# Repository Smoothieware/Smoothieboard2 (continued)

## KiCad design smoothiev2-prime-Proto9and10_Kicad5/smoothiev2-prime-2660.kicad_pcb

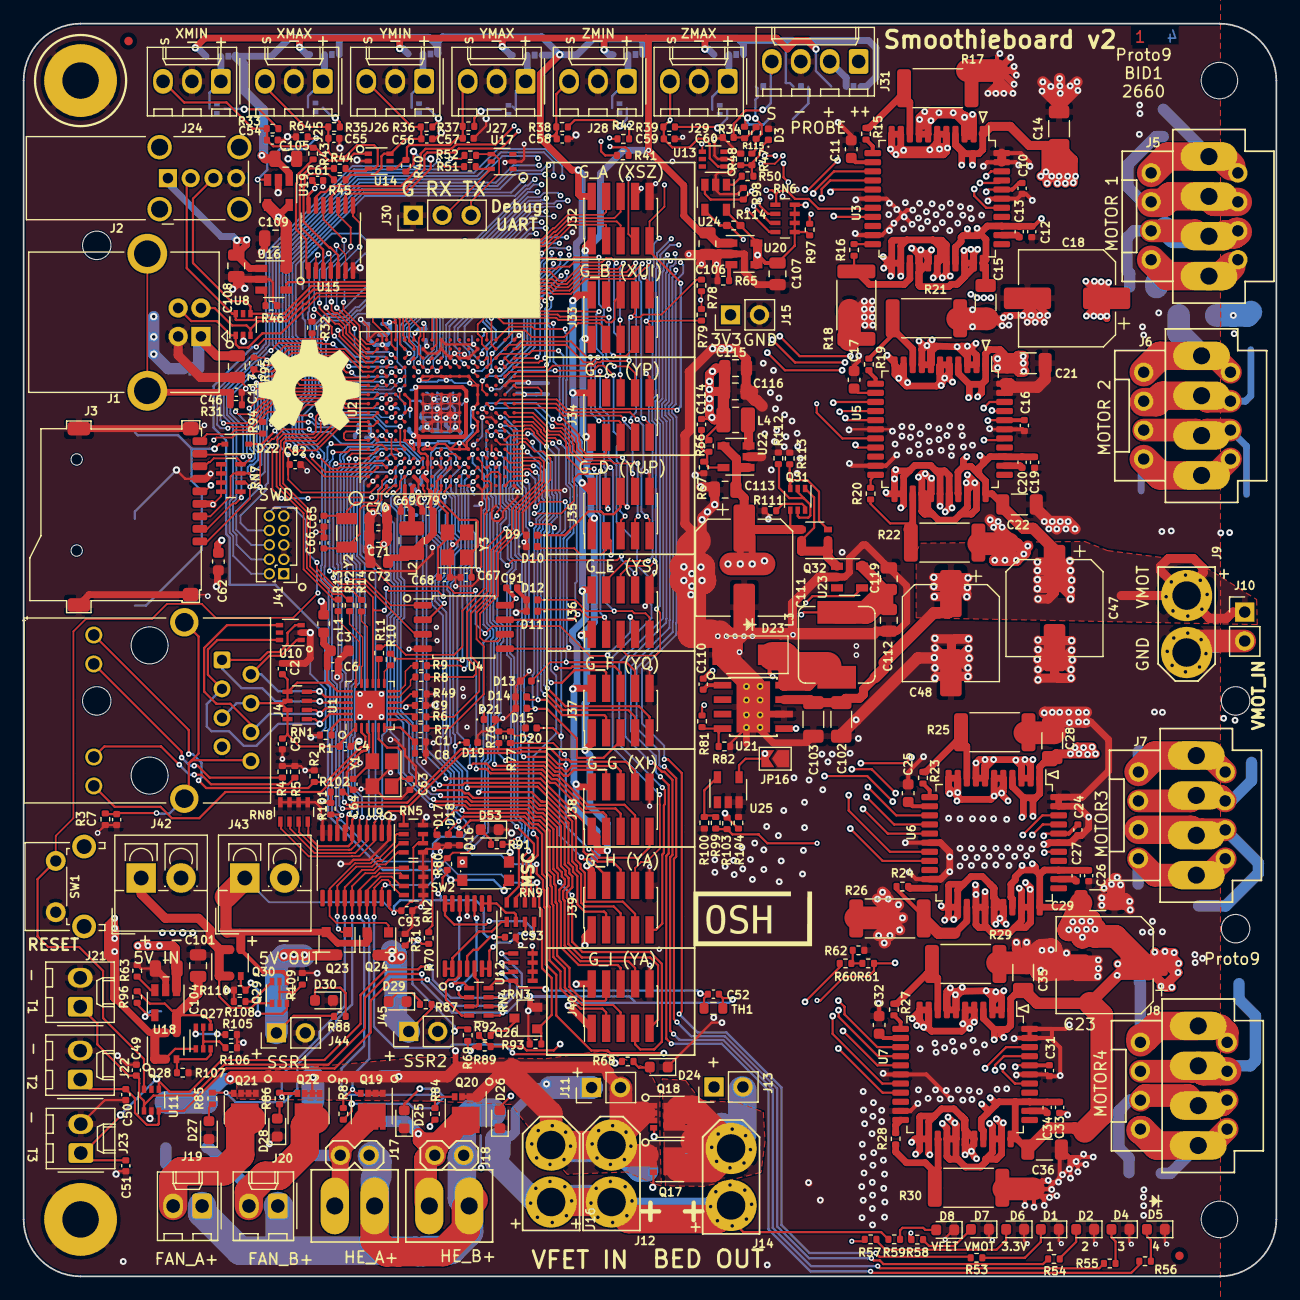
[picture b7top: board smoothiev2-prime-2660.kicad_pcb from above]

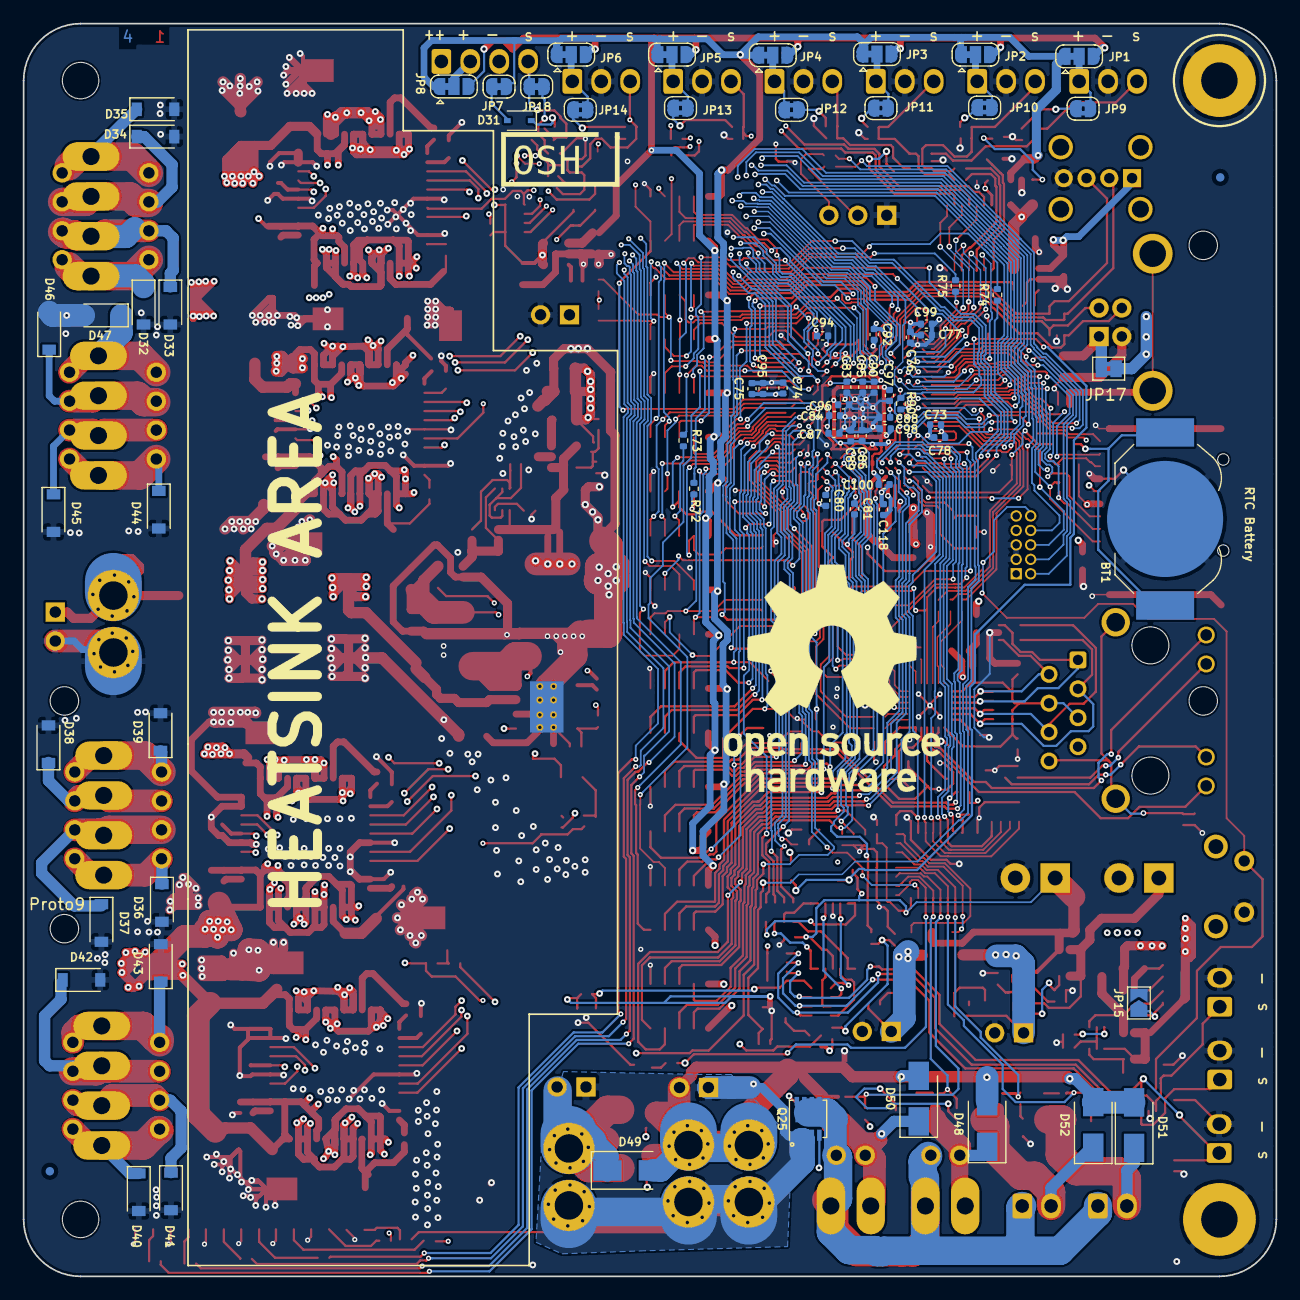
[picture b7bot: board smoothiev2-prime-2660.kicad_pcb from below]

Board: 4 copper layers, 110.0 x 110.0 mm, 427 parts (75 on the bottom side), 345 nets.

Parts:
BT1: DNP; BatteryHolder_LINX_BAT-HLD-012-SMT
C1: 470p; C_0402_1005Metric
C2, C4, C5, C6, C9, C12, C19, C26, C33, C54, C55, C56, C57, C58, C59, C60, C81: 100n; C_0402_1005Metric
C3, C11, C17, C25, C32, C62, C70, C71, C72: 10u; C_0603_1608Metric
C7, C46: DNP; C_0402_1005Metric
C8, C10, C13, C16, C20, C24, C27, C31, C34, C49, C50, C51, C52, C53, C61, C73, C74, C75, C76, C77, C78, C79, C80, C82, C83, C84, C85, C86, C87, C88, C89, C90, C91, C92, C93, C94, C95, C96, C97, C98, C99, C100, C118: 1u; C_0402_1005Metric
C14, C15, C21, C22, C28, C29, C35, C36, C102, C103: 10u; C_1206_3216Metric
C18, C23, C47, C48, C111: CP; CP_Elec_8x11.9
C63, C64, C65, C66, C67, C68: 5.6p; C_0402_1005Metric
C69: 220p; C_0402_1005Metric
C101, C104, C105, C106, C107, C108, C109, C112, C113, C115, C116, C117, C119: 22u; C_0805_2012Metric
C110: 10n; C_0402_1005Metric
C114: 22p; C_0402_1005Metric
D1, D2, D4, D5, D6, D7, D8, D24, D25, D26, D27, D28, D29, D30, D53: LED; LED_0603_1608Metric
D3, D9, D10, D11, D12, D13, D14, D15, D16, D17, D18, D19, D20, D21: LESD8D3.3CAT5G; D_0402_1005Metric
D22: B5817WS; D_SOD-323
D23, D48, D49, D50, D51, D52: B340A; D_SMA
D31: D; D_SOD-323
D32, D33, D34, D35, D36, D37, D38, D39, D40, D41, D42, D43, D44, D45, D46, D47: SJD12C30L01; D_SOD-123
FID1, FID2, FID3, FID4: Fiducial; Fiducial_0.75mm_Mask1.5mm
H1, H2: MountingHole; MountingHole_3.2mm_M3
H3, H4: MountingHole_Pad; MountingHole_3.2mm_M3_Pad
H5, H6, H7, H8: MountingHole; Stencil8_2.5mm
J1: USB_B; USB_B_OST_USB-B1HSxx_Horizontal
J2: USB_A; USB_A_Wuerth_614004134726_Horizontal
J3: Micro_SD_Card_Det; TF-01A
J4: RJ45_Hanrun_HR911105A
J5, J6, J7, J8: Screw_Terminal_01x04; CONN_MOTOR2
J9, J12, J14, J16: Conn_01x02; XT30
J10, J11, J13, J15, J44, J45: Conn_01x02; PinHeader_1x02_P2.54mm_Vertical
J17, J18: Conn_01x02; CONN_SFET
J19, J20, J21, J22, J23: Conn_01x02; Molex_KK-254_AE-6410-02A_1x02_P2.54mm_Vertical
J24, J25, J26, J27, J28, J29: Conn_01x03; Molex_KK-254_AE-6410-03A_1x03_P2.54mm_Vertical
J30: Conn_01x03_Male; PinHeader_1x03_P2.54mm_Vertical
J31: Conn_01x04; Molex_KK-254_AE-6410-04A_1x04_P2.54mm_Vertical
J32, J33, J34, J35, J36, J37, J38, J39, J40: Conn_02x05_Odd_Even; PinHeader_2x05_P1.27mm_Vertical_SMD
J41: Conn_ARM_JTAG_SWD_10; PinHeader_2x05_P1.27mm_Vertical
J42, J43: Conn_01x02; TerminalBlock_4Ucon_1x02_P3.50mm_Vertical
JP1, JP2, JP3, JP4, JP5, JP6, JP8: SolderJumper_3_Bridged12; SolderJumper-3_P1.3mm_Bridged12_RoundedPad1.0x1.5mm
JP7: SolderJumper_2_Bridged; SolderJumper-2_P1.3mm_Bridged_RoundedPad1.0x1.5mm
JP9, JP10, JP11, JP12, JP13, JP14: SolderJumper_2_Bridged; SolderJumper-2_P1.3mm_Bridged2Bar_RoundedPad1.0x1.5mm
JP15, JP16: SolderJumper_2_Open; SolderJumper-2_P1.3mm_Open_TrianglePad1.0x1.5mm
JP17: SolderJumper_2_Bridged; SolderJumper-2_P1.3mm_Bridged2Bar_Pad1.0x1.5mm
JP18: Jumper_NC_Small; SolderJumper-2_P1.3mm_Bridged_RoundedPad1.0x1.5mm
L1: CBG160808U601T; L_0603_1608Metric
L2, L4: MHCD252012A-2R2M-A8S; L_1008_2520Metric
L3: YSPI0630A-220M; L_Sumida_CDMC6D28_7.25x6.5mm
LOGO1: Logo_Open_Hardware_Small; OSHW-Logo_19x20mm_SilkScreen
LOGO2: Logo_Open_Hardware_Small; OSHW-Symbol_8.9x8mm_SilkScreen
LOGO3, LOGO4: Logo_Open_Hardware_Small; OSHW_Dual_0.25_Scale
NT1, NT2, NT3, NT4, NT5, NT6, NT7, NT8: Net-Tie_2; NetTie-2_SMD_Pad2.0mm
NT9, NT11: Net-Tie_2; NetTie-2_SMD_Pad0.5mm
Q17, Q18, Q19, Q20, Q21, Q22: WSD3066DN33; VSON-8_3.3x3.3mm_P0.65mm_NexFET
Q23, Q24: CJ2301 S1; SOT-23
Q25: WSD30L40DN; Vishay_PowerPAK_1212-8_Single
Q26: 2N7002; SOT-23
Q27, Q29, Q31: MBT3906DW1; SOT-363_SC-70-6
Q28, Q30, Q32: SQ3493EV; TSOP-6_1.65x3.05mm_P0.95mm
R1: 12.1k; R_0402_1005Metric
R2, R32, R33, R35, R36, R37, R38, R39, R49, R58, R59, R62, R71, R81, R90, R92, R93, R94, R95, R96, R101, R102, R105, R107, R108, R110, R111, R113: 10k; R_0402_1005Metric
R3, R31: DNP; R_0402_1005Metric
R4, R5, R34, R40, R41, R42, R43, R44, R45, R48, R50, R53, R54, R55, R56, R57, R60, R68, R70, R76, R77, R78, R79, R83, R84, R85, R86, R87, R88, R91, R98: 1k; R_0402_1005Metric
R6, R7, R8, R9, R10, R11, R12, R13, R14: 33R; R_0402_1005Metric
R15, R16, R19, R20, R23, R24, R27, R28: 47R; R_0402_1005Metric
R17, R18, R21, R22, R25, R26, R29, R30: R; R_2512_6332Metric
R46, R63, R67, R80: 4.7k; R_0402_1005Metric
R47, R104, R115: 7.1k; R_0402_1005Metric
R51, R52, R72, R73, R74, R75: 100R; R_0402_1005Metric
R61, R69, R106, R109, R112: 100k; R_0402_1005Metric
R64, R65, R66, R89, R100: 21.5k; R_0402_1005Metric
R82: 3.24k; R_0402_1005Metric
R97: 8.2k; R_0402_1005Metric
R99: 56k; R_0402_1005Metric
R103: 33k; R_0402_1005Metric
R114: 3.24k; R_0402_1005Metric_Pad0.72x0.64mm_HandSolder
RN1: 49.9R; R_Array_Concave_4x0603
RN2, RN5, RN6, RN7, RN8: 10k; R_Array_Concave_4x0603
RN3, RN4, RN9: 4.7k; R_Array_Concave_4x0603
SW1: SW_Push; SW_Tactile_SPST_Angled_PTS645Vx58-2LFS
SW2: TS-1185EC-C-D-B; SW_Push_1P1T_NO_CK_KMR2
TH1: R_0603_1608Metric
U1: LAN8720A; QFN-24-1EP_4x4mm_P0.5mm_EP2.6x2.6mm
U2: STM32H745XIHx; TFBGA-265_14x14mm_Layout17x17_P0.8mm
U3, U5, U6, U7: TMC2660; LQFP-44_10x10mm_P0.8mm
U4: AT25SF081-SSHF-X; SOIC-8_5.23x5.23mm_P1.27mm
U8, U10, U11, U13, U14, U17: TPD4E1U06DCKR; SOT-363_SC-70-6
U9: 74HCT541; TSSOP-20_4.4x6.5mm_P0.65mm
U12: LMV324; TSSOP-14_4.4x5mm_P0.65mm
U15: 74LCX07; TSSOP-14_4.4x5mm_P0.65mm
U16, U18, U19, U20: MT9700; SOT-23-5
U21: TPS5430DDA; TI_SO-PowerPAD-8_ThermalVias
U22: MT3410L; SOT-23-5
U23: AP22814AW5; SOT-23-5
U24: LMV331; SOT-23-5
U25: BD4722G; SOT-23-5
Y1, Y3: Crystal_GND24; Crystal_SMD_3225-4Pin_3.2x2.5mm
Y2: Crystal; Crystal_SMD_3215-2Pin_3.2x1.5mm

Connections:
/1.2V_MCU: C72.1, C73.1, C74.1, C75.1, C76.1, C77.1, C78.1, C79.1, C95.1, C96.1, C97.1, C98.1, C99.1, C100.1, L2.1, U2.A6, U2.A7, U2.C17, U2.D17, U2.G2, U2.U11, U2.U12
/3V3: C9.1, C10.1, C16.1, C24.1, C31.1, C61.1, C62.1, C70.1, C71.1, C80.1, C83.1, C84.1, C85.1, C86.1, C87.1, C88.1, C89.1, C90.1, C91.1, C92.1, C94.1, C107.1, C114.2, C115.1, C116.1, C118.1, J3.4, J15.1, J41.1, L1.2, L4.1, R57.1, R66.1, R76.2, R77.2, R78.2, R79.2, R94.2, R95.2, R97.2, R101.2, R102.2, R114.1, RN3.5, RN3.6, RN3.7, RN3.8, RN6.5, RN6.6, RN6.7, RN6.8, RN7.1, RN7.2, RN7.3, RN7.4, SW2.2, U1.9, U2.E6, U2.E7, U2.E9, U2.E11, U2.F1, U2.F5, U2.F17, U2.G5, U2.G13, U2.G17, U2.H5, U2.H13, U2.J13, U2.K5, U2.K13, U2.L1, U2.L5, U2.L13, U2.M1, U2.M5, U2.M13, U2.N7, U2.N8, U2.N10, U2.N11, U2.N12, U2.P17, U3.40, U4.8, U5.40, U6.40, U7.40, U15.14, U20.4, U20.5, U24.5
/3V3_LIMIT: C106.1, J32.1, J33.1, J34.1, J35.1, J36.1, J37.1, J38.1, J39.1, J40.1, JP1.3, JP2.3, JP3.3, JP4.3, JP5.3, JP6.3, JP8.3, U20.1
/5V: C53.1, C93.1, C104.1, C109.1, C111.1, C113.1, J43.1, Q23.2, Q24.2, Q29.4, Q30.4, Q31.4, Q32.4, R80.2, RN5.2, RN5.3, U9.20, U12.4, U16.5, U18.1, U19.4, U19.5, U22.1, U22.4
/5VPORTIN: J42.1, Q29.1, Q30.1, Q30.2, Q30.5, Q30.6
/5V_IN: JP17.2, Q27.1, Q28.1, Q28.2, Q28.5, Q28.6
/5V_LIMIT: C105.1, J32.2, J33.2, J34.2, J35.2, J36.2, J37.2, J38.2, J39.2, J40.2, JP1.1, JP2.1, JP3.1, JP4.1, JP5.1, JP6.1, JP7.1, JP8.1, U19.1
/ADC1_CH12: D19.1, J39.5, U2.M3
/ADC1_CH13: D21.1, J39.3, U2.M4
/ADC1_CH15: D20.1, J39.4, U2.U2
/ADC3_CH6: D16.1, J40.3, U2.L3
/ADC3_CH8: D17.1, J40.4, U2.K2
/ADC3_CH9: D18.1, J40.5, U2.J5
/BED_FET: RN5.5, U2.D3, U9.2
/BOOT0: R32.2, R90.2, SW2.1, U2.E8
/CARD_DET: J3.9, R94.1, U2.A9
/CS_A: RN6.1, U2.E10, U3.18
/CS_B: RN6.4, U2.F15, U5.18
/CS_C: RN6.3, U2.F16, U6.18
/CS_D: RN6.2, U2.G15, U7.18
/DIR_A: U2.A12, U3.41
/DIR_B: U2.H16, U5.41
/DIR_C: U2.H14, U6.41
/DIR_D: U2.G14, U7.41
/ESXMAX: U2.C14, U15.4
/ESXMIN: U2.D13, U15.2
/ESYMAX: U2.D15, U15.8
/ESYMIN: U2.A15, U15.6
/ESZMAX: U2.B16, U15.12
/ESZMIN: U2.A16, U15.10
/ETH_CRSDV: R8.2, U2.R5
/ETH_MDC: R10.2, U2.M2
/ETH_MDIO: R9.2, U2.N3
/ETH_RFCLK: R11.2, U2.N4
/ETH_RXD0: R6.2, U2.T4
/ETH_RXD1: R7.2, U2.U4
/ETH_TXD0: R12.2, U2.D9
/ETH_TXD1: R13.2, U2.C9
/ETH_TXEN: R14.2, U2.B9
/EXTRAFET: Q26.1, R93.2, U2.C11
/FANA_FET: RN8.7, U2.B4, U9.5
/FANB_FET: RN8.8, U2.F4, U9.6
/FETSENSE: R70.1, U2.K4
/HOTEND_A_FET: RN8.5, U2.C4, U9.3
/HOTEND_B_FET: RN8.6, U2.D5, U9.4
/I2C2_SCL: J38.9, R77.1, U2.G3
/I2C2_SDA: J38.8, R76.1, U2.G4
/I2C3_SCL: J33.9, R79.1, U2.E15
/I2C3_SDA: J33.8, R78.1, U2.T13
/ILED1: R53.1, U2.R13
/ILED2: R54.1, U2.P13
/ILED3: R55.1, U2.P14
/ILED4: R56.1, U2.R14
/MCU_DEBUG_RX: R51.1, U2.B11
/MCU_DEBUG_TX: R52.1, U2.A11
/MCU_RESET: C81.1, J41.10, SW1.2, U1.15, U2.K1, U11.6
/MOTSPI_CIPO: J32.8, U2.D1, U3.14, U5.14, U6.14, U7.14
/MOTSPI_COPI: J32.7, U2.E5, U3.15, U5.15, U6.15, U7.15
/MOTSPI_SCK: J32.9, U2.R10, U3.16, U5.16, U6.16, U7.16
/MOT_EN: U2.D16, U3.19, U5.19, U6.19, U7.19
/OUTPUTENABLE: R80.1, U2.P8, U9.19
/PA4: D15.1, J37.5, U2.U3
/PB1: D14.1, J37.3, U2.T5
/PB12: J39.9, U2.T14
/PC0: J38.5, U2.L2
/PC13: J40.9, U2.E3
/PD9: J33.3, U2.T17
/PD10: J34.5, U2.T16
/PD12: J34.4, U2.R16
/PD14: J34.3, U2.P16
/PD15: J36.6, U2.P15
/PE4: J40.7, U2.D2
/PE7: D10.2, J35.3, U2.U9
/PE8: D11.1, J36.3, U2.T9
/PF2: J39.6, U2.G1
/PF13: R91.1, U2.P7
/PF15: J38.6, U2.R9
/PG0: J37.6, U2.T8
/PG1: D13.1, J37.8, U2.U8
/PH2: J38.3, U2.N2
/PH3: J38.7, U2.P2
/PH4: J38.4, U2.P3
/PH7: J39.8, U2.U13
/PI8: J40.6, U2.E4
/PI9: J40.8, U2.E2
/PI10: J39.7, U2.F3
/PJ2: J37.9, U2.T6
/PJ3: J37.7, U2.U6
/PJ4: J37.4, U2.U7
/PJ6: J32.3, U2.N15
/PJ7: J36.4, U2.N14
/PJ8: J36.5, U2.N13
/PJ9: J32.4, U2.M14
/PJ10: J32.5, U2.L14
/PJ11: J32.6, U2.K14
/PK0: J33.6, U2.J14
/PK1: J33.7, U2.J15
/PROBE: R114.2, U2.P11, U24.4
/QSPI_CS: U2.B5, U4.1
/QSPI_IO0: U2.R15, U4.5
/QSPI_IO1: U2.L4, U4.2
/QSPI_IO2: U2.C3, U4.3
/QSPI_IO3: U2.R17, U4.7
/QSPI_SCK: U2.R6, U4.6
/SD_CK: J3.5, U2.C12
/SD_CMD: J3.3, RN7.7, U2.D12
/SD_D0: J3.7, RN7.8, U2.E13
/SD_D1: J3.8, R95.1, U2.E14
/SD_D2: J3.1, RN7.6, U2.A13
/SD_D3: J3.2, RN7.5, U2.B13
/SG_A: U2.B8, U3.38
/SG_B: U2.A8, U5.38
/SG_C: U2.B10, U6.38
/SG_D: U2.A10, U7.38
/SPI1_CIPO: J36.8, U2.R3
/SPI1_COPI: J36.7, U2.A5
/SPI1_SCK: D12.1, J36.9, U2.T3
/SSR1: R102.1, U2.A4, U9.7
/SSR2: R101.1, U2.C5, U9.8
/STEP_A: U2.B12, U3.42
/STEP_B: U2.H17, U5.42
/STEP_C: U2.H15, U6.42
/STEP_D: U2.F14, U7.42
/SWCLK: J41.4, U2.B14
/SWDIO: J41.2, U2.C15
/SWO: J41.6, U2.C6
/T1: RN9.1, U2.T1
/T2: RN9.2, U2.R7
/T3: RN9.3, U2.U5
/T4: RN9.4, U2.T7
/TDI: J41.8, U2.A14
/TIM1_CH1: D9.1, J35.6, U2.P9
/TIM1_CH2: J35.7, U2.P10
/TIM1_CH3: J35.8, U2.T10
/TIM1_CH4: J35.9, U2.U10
/TIM8_CH1: J34.6, U2.A3
/TIM8_CH2: J34.7, U2.A2
/TIM8_CH3: J34.8, U2.B3
/TIM8_CH4: J34.9, U2.B15
/USART3_RX: R73.1, U2.P12
/USART3_TX: R72.1, U2.U16
/USART4_RX: R75.1, U2.B17
/USART4_TX: R74.1, U2.D4
/USB_DEV_D+: J1.3, U2.E16, U8.1
/USB_DEV_D-: J1.2, U2.E17, U8.3
/USB_HOST_D+: J2.3, U2.T15, U8.4
/USB_HOST_D-: J2.2, U2.U15, U8.6
/USB_PWR: C108.1, J2.1, U16.1
/USB_PWR_ON: U2.U14, U16.4
/VBAT: C82.1, D22.1, U2.B1
/VLX: C69.1, L2.2, U2.E1
/VMOT: C12.1, C13.1, C14.1, C15.1, C18.1, C19.1, C20.1, C21.1, C22.1, C23.1, C26.1, C27.1, C28.1, C29.1, C33.1, C34.1, C35.1, C36.1, C47.1, C48.1, C102.1, C103.1, J9.1, J10.1, J31.1, R58.1, R61.1, R99.2, R103.1, U3.1, U3.4, U3.30, U3.33, U3.36, U5.1, U5.4, U5.30, U5.33, U5.36, U6.1, U6.4, U6.30, U6.33, U6.36, U7.1, U7.4, U7.30, U7.33, U7.36, U21.7
/VMOTSENSE: R60.2, U2.P4
/XTAL_HSE_IN: C68.1, U2.J2, Y3.3
/XTAL_HSE_OUT: C67.1, U2.J1, Y3.1
/XTAL_LSE_IN: C65.1, U2.C2, Y2.1
/XTAL_LSE_OUT: C66.1, U2.C1, Y2.2
/driver-a-2660/COIL_A1: D35.1, J5.4, U3.2, U3.3, U3.7, U3.8
/driver-a-2660/COIL_A2: D34.1, J5.3, U3.5, U3.6, U3.10, U3.11
/driver-a-2660/COIL_B1: D33.1, J5.2, U3.26, U3.27, U3.31, U3.32
/driver-a-2660/COIL_B2: D32.1, J5.1, U3.23, U3.24, U3.28, U3.29
/ethernet/ETH_REFGND: C7.1, J4.8, J4.SH, R3.1
/ethernet/LED1: J4.12, U1.3
/ethernet/LED2: J4.9, R2.1, U1.2
/ethernet/TXD0: R12.1, U1.17
/ethernet/TXD1: R13.1, U1.18
/ethernet/TXEN: R14.1, U1.16
/expansion/GB_4: J33.4, R74.2
/expansion/GB_5: J33.5, R75.2
/expansion/GD_4: J35.4, R72.2
/expansion/GD_5: J35.5, R73.2
/mosfets/BED_GATE: Q17.4, Q18.4, R68.2, RN2.8, U9.18
/mosfets/CUTOFF_GATE: Q26.3, R92.1
/mosfets/FAN2_GATE: Q22.4, R86.2, RN5.8, U9.14
/mosfets/FAN_GATE: Q21.4, R85.2, RN2.5, U9.15
/mosfets/GND_FET: D48.2, D49.2, D50.2, D51.2, D52.2, J11.2, J12.2, J16.2, NT9.2, Q17.1, Q17.2, Q17.3, Q18.1, Q18.2, Q18.3, Q19.1, Q19.2, Q19.3, Q20.1, Q20.2, Q20.3, Q21.1, Q21.2, Q21.3, Q22.1, Q22.2, Q22.3
/mosfets/HEA_GATE: Q19.4, R83.2, RN2.7, U9.17
/mosfets/HEB_GATE: Q20.4, R84.2, RN2.6, U9.16
/mosfets/SSR1_G: Q23.1, RN5.7, U9.13
/mosfets/SSR2_G: Q24.1, RN5.6, U9.12
/mosfets/SW_BED: D49.1, J13.2, J14.2, Q17.5, Q18.5
/mosfets/VFET: J11.1, J12.1, J13.1, J14.1, J16.1, Q25.1, Q25.2, Q25.3, R59.1, R69.2, R89.2
/power/5v_REG: Q31.1, Q32.1, Q32.2, Q32.5, Q32.6, U23.1
/power/USB_IN: C101.1, Q27.4, Q28.4, R96.2, U18.5
/power/UVLO: JP16.2, R103.2, R104.1, U21.5, U23.4, U25.4
/sheet622B088E/COIL_A1: D39.1, J7.4, U6.2, U6.3, U6.7, U6.8
/sheet622B088E/COIL_A2: D38.1, J7.3, U6.5, U6.6, U6.10, U6.11
/sheet622B088E/COIL_B1: D37.1, J7.2, U6.26, U6.27, U6.31, U6.32
/sheet622B088E/COIL_B2: D36.1, J7.1, U6.23, U6.24, U6.28, U6.29
/sheet622F7158/COIL_A1: D43.1, J8.4, U7.2, U7.3, U7.7, U7.8
/sheet622F7158/COIL_A2: D42.1, J8.3, U7.5, U7.6, U7.10, U7.11
/sheet622F7158/COIL_B1: D41.1, J8.2, U7.26, U7.27, U7.31, U7.32
/sheet622F7158/COIL_B2: D40.1, J8.1, U7.23, U7.24, U7.28, U7.29
/sheet62266892/COIL_A1: D47.1, J6.4, U5.2, U5.3, U5.7, U5.8
/sheet62266892/COIL_A2: D46.1, J6.3, U5.5, U5.6, U5.10, U5.11
/sheet62266892/COIL_B1: D45.1, J6.2, U5.26, U5.27, U5.31, U5.32
/sheet62266892/COIL_B2: D44.1, J6.1, U5.23, U5.24, U5.28, U5.29
GND: BT1.2, C1.2, C2.2, C3.2, C4.2, C5.2, C6.2, C7.2, C8.2, C9.2, C10.2, C11.2, C12.2, C14.2, C15.2, C16.2, C17.2, C18.2, C19.2, C21.2, C22.2, C23.2, C24.2, C25.2, C26.2, C28.2, C29.2, C31.2, C32.2, C33.2, C35.2, C36.2, C46.2, C47.2, C48.2, C49.2, C50.2, C51.2, C53.2, C54.2, C55.2, C56.2, C57.2, C58.2, C59.2, C60.2, C61.2, C62.2, C63.2, C64.2, C65.2, C66.2, C67.2, C68.2, C69.2, C70.2, C71.2, C72.2, C73.2, C74.2, C75.2, C76.2, C77.2, C78.2, C79.2, C80.2, C81.2, C82.2, C83.2, C84.2, C85.2, C86.2, C87.2, C88.2, C89.2, C90.2, C91.2, C92.2, C93.2, C94.2, C95.2, C96.2, C97.2, C98.2, C99.2, C100.2, C101.2, C102.2, C103.2, C104.2, C105.2, C106.2, C107.2, C108.2, C109.2, C111.2, C112.2, C113.2, C115.2, C116.2, C117.2, C118.2, C119.2, D1.1, D2.1, D3.2, D4.1, D5.1, D6.1, D7.1, D8.1, D9.2, D10.1, D11.2, D12.2, D13.2, D14.2, D15.2, D16.2, D17.2, D18.2, D19.2, D20.2, D21.2, D23.2, D24.1, D25.1, D26.1, D27.1, D28.1, D29.1, D30.1, D32.2, D33.2, D34.2, D35.2, D36.2, D37.2, D38.2, D39.2, D40.2, D41.2, D42.2, D43.2, D44.2, D45.2, D46.2, D47.2, D53.1, H3.1, H4.1, J1.4, J2.4, J3.6, J3.10, J3.11, J9.2, J10.2, J15.2, J21.2, J22.2, J23.2, J24.2, J25.2, J26.2, J27.2, J28.2, J29.2, J30.1, J31.3, J32.10, J33.10, J34.10, J35.10, J36.10, J37.10, J38.10, J39.10, J40.10, J41.3, J41.5, J41.9, J42.2, J43.2, J44.2, J45.2, JP15.2, JP16.1, NT1.2, NT2.2, NT3.2, NT4.2, NT5.2, NT6.2, NT7.2, NT8.2, NT9.1, NT11.2, Q26.2, R1.2, R2.2, R3.2, R4.1, R5.1, R31.2, R32.1, R46.2, R48.1, R49.2, R62.2, R63.2, R64.2, R65.2, R67.2, R71.1, R82.2, R93.1, R98.1, R100.1, R104.2, R105.2, R106.2, R107.2, R108.2, R109.2, R110.2, R111.2, R112.2, R113.2, RN2.1, RN2.2, RN2.3, RN2.4, RN5.1, RN5.4, RN8.1, RN8.2, RN8.3, RN8.4, SW1.1, U1.25, U2.A1, U2.A17, U2.B2, U2.B6, U2.C10, U2.C13, U2.C16, U2.F2, U2.G7, U2.G8, U2.G9, U2.G10, U2.G11, U2.G16, U2.H7, U2.H8, U2.H9, U2.H10, U2.H11, U2.J3, U2.J7, U2.J8, U2.J9, U2.J10, U2.J11, U2.J16, U2.J17, U2.K3, U2.K7, U2.K8, U2.K9, U2.K10, U2.K11, U2.K15, U2.L7, U2.L8, U2.L9, U2.L10, U2.L11, U2.L15, U2.M15, U2.N1, U2.N16, U2.P1, U2.R4, U2.R8, U2.T12, U2.U1, U2.U17, U3.17, U3.21, U3.39, U3.43, U3.44, U4.4, U5.17, U5.21, U5.39, U5.43, U5.44, U6.17, U6.21, U6.39, U6.43, U6.44, U7.17, U7.21, U7.39, U7.43, U7.44, U8.2, U9.1, U9.9, U9.10, U10.2, U11.2, U12.11, U13.2, U14.2, U15.7, U16.2, U17.2, U18.2, U19.2, U20.2, U21.6, U21.9, U22.2, U23.2, U24.2, U25.2, U25.3, Y1.2, Y1.4, Y3.2, Y3.4
unnamed: BT1.1, D22.2
unnamed: C1.1, C8.1, U1.6
unnamed: C2.1, C3.1, C4.1, C5.1, C6.1, J4.4, J4.5, L1.1, RN1.5, RN1.6, RN1.7, RN1.8, U1.1, U1.19
unnamed: C11.1, U3.13
unnamed: C13.2, U3.35
unnamed: C17.1, U5.13
unnamed: C20.2, U5.35
unnamed: C25.1, U6.13
unnamed: C27.2, U6.35
unnamed: C32.1, U7.13
unnamed: C34.2, U7.35
unnamed: C46.1, J1.5, J2.5, R31.1
unnamed: C49.1, J21.1, RN3.1, RN4.1, U11.1
unnamed: C50.1, J22.1, RN3.2, RN4.2, U11.3
unnamed: C51.1, J23.1, RN3.3, RN4.3, U11.4
unnamed: C52.1, RN3.4, RN4.4, TH1.1
unnamed: C52.2, NT11.1, TH1.2
unnamed: C54.1, J24.3, R33.2, R43.2, U14.1
unnamed: C55.1, J25.3, R35.2, R44.2, U14.3
unnamed: C56.1, J26.3, R36.2, R45.2, U14.6
unnamed: C57.1, J27.3, R37.2, R40.2, U14.4
unnamed: C58.1, J28.3, R38.2, R41.2, U13.4
unnamed: C59.1, J29.3, R39.2, R42.2, U13.1
unnamed: C60.1, J31.4, JP18.1, R34.2, R115.2
unnamed: C63.1, U1.5, Y1.1
unnamed: C64.1, U1.4, Y1.3
unnamed: C110.1, D23.1, L3.2, U21.8
unnamed: C110.2, U21.1
unnamed: C112.1, C119.1, L3.1, R81.1, U23.5
unnamed: C114.1, R66.2, R67.1, U22.5
unnamed: C117.1, J1.1, JP17.1
unnamed: D1.2, R53.2
unnamed: D2.2, R54.2
unnamed: D3.1, R47.1, R48.2, R50.2
unnamed: D4.2, R55.2
unnamed: D5.2, R56.2
unnamed: D6.2, R57.2
unnamed: D7.2, R58.2
unnamed: D8.2, R59.2
unnamed: D24.2, R68.1
unnamed: D25.2, R83.1
unnamed: D26.2, R84.1
unnamed: D27.2, R85.1
unnamed: D28.2, R86.1
unnamed: D29.2, R87.2
unnamed: D30.2, R88.2
unnamed: D31.1, R34.1
unnamed: D31.2, JP7.2
unnamed: D48.1, J17.2, Q19.5
unnamed: D50.1, J18.2, Q20.5
unnamed: D51.1, J19.2, Q21.5
unnamed: D52.1, J20.2, Q22.5
unnamed: D53.2, R91.2
unnamed: J4.1, RN1.3, U1.21, U10.3
unnamed: J4.2, RN1.4, U1.20, U10.1
unnamed: J4.3, RN1.1, U1.23, U10.6
unnamed: J4.6, RN1.2, U1.22, U10.4
unnamed: J4.10, R4.2
unnamed: J4.11, R5.2
unnamed: J17.1, J18.1, J19.1, J20.1, Q25.5
unnamed: J24.1, JP1.2, JP9.1
unnamed: J25.1, JP2.2, JP10.1
unnamed: J26.1, JP3.2, JP11.1
unnamed: J27.1, JP4.2, JP12.1
unnamed: J28.1, JP5.2, JP13.1
unnamed: J29.1, JP6.2, JP14.1
unnamed: J30.2, R51.2, U17.6
unnamed: J30.3, R52.2, U17.4
unnamed: J31.2, JP8.2
unnamed: J44.1, Q23.3, R88.1
unnamed: J45.1, Q24.3, R87.1
unnamed: JP9.2, R33.1
unnamed: JP10.2, R35.1
unnamed: JP11.2, R36.1
unnamed: JP12.2, R37.1
unnamed: JP13.2, R38.1
unnamed: JP14.2, R39.1
unnamed: JP15.1, R96.1, U18.4
unnamed: JP18.2, R47.2, R115.1
unnamed: L4.2, U22.3
unnamed: NT1.1, R17.1
unnamed: NT2.1, R18.1
unnamed: NT3.1, R21.1
unnamed: NT4.1, R22.1
unnamed: NT5.1, R25.1
unnamed: NT6.1, R26.1
unnamed: NT7.1, R29.1
unnamed: NT8.1, R30.1
unnamed: Q25.4, R89.1, R92.2
unnamed: Q27.2, Q27.5, R106.1
unnamed: Q27.3, Q28.3, R107.1
unnamed: Q27.6, R105.1
unnamed: Q29.2, Q29.5, R109.1
unnamed: Q29.3, Q30.3, R110.1
unnamed: Q29.6, R108.1
unnamed: Q31.2, Q31.5, R112.1
unnamed: Q31.3, Q32.3, R113.1
unnamed: Q31.6, R111.1
unnamed: R1.1, U1.24
unnamed: R6.1, U1.8
unnamed: R7.1, U1.7
unnamed: R8.1, U1.11
unnamed: R9.1, U1.12
unnamed: R10.1, U1.13
unnamed: R11.1, U1.14
unnamed: R15.1, R17.2, U3.9
unnamed: R15.2, U3.12
unnamed: R16.1, R18.2, U3.25
unnamed: R16.2, U3.22
unnamed: R19.1, R21.2, U5.9
unnamed: R19.2, U5.12
unnamed: R20.1, R22.2, U5.25
unnamed: R20.2, U5.22
unnamed: R23.1, R25.2, U6.9
unnamed: R23.2, U6.12
unnamed: R24.1, R26.2, U6.25
unnamed: R24.2, U6.22
unnamed: R27.1, R29.2, U7.9
unnamed: R27.2, U7.12
unnamed: R28.1, R30.2, U7.25
unnamed: R28.2, U7.22
unnamed: R40.1, U15.9
unnamed: R41.1, U15.11
unnamed: R42.1, U15.13
unnamed: R43.1, U15.1
unnamed: R44.1, U15.3
unnamed: R45.1, U15.5
unnamed: R46.1, U16.3
unnamed: R49.1, U1.10
unnamed: R50.1, U24.1
unnamed: R60.1, R61.2, R62.1
unnamed: R63.1, U18.3
unnamed: R64.1, U19.3
unnamed: R65.1, U20.3
unnamed: R69.1, R70.2, R71.2
unnamed: R81.2, R82.1, U21.4
unnamed: R90.1, U2.D10
unnamed: R97.1, R98.2, U24.3
unnamed: R99.1, R100.2, U25.5
unnamed: RN4.5, U12.12
unnamed: RN4.6, U12.10
unnamed: RN4.7, U12.5
unnamed: RN4.8, U12.3
unnamed: RN9.5, U12.1, U12.2
unnamed: RN9.6, U12.8, U12.9
unnamed: RN9.7, U12.6, U12.7
unnamed: RN9.8, U12.13, U12.14
